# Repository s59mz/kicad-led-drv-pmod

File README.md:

# led_drv_pmod
PMOD PCB module for LTC3206 LED driver 

Schematic:
[led_drv_pmod.pdf](led_drv_pmod.pdf)

BOM:
[led_drv_pmod.csv](led_drv_pmod.csv)

Gerbers:
[gerbers.zip](https://github.com/s59mz/kicad-led-drv-pmod/raw/main/gerbers.zip)

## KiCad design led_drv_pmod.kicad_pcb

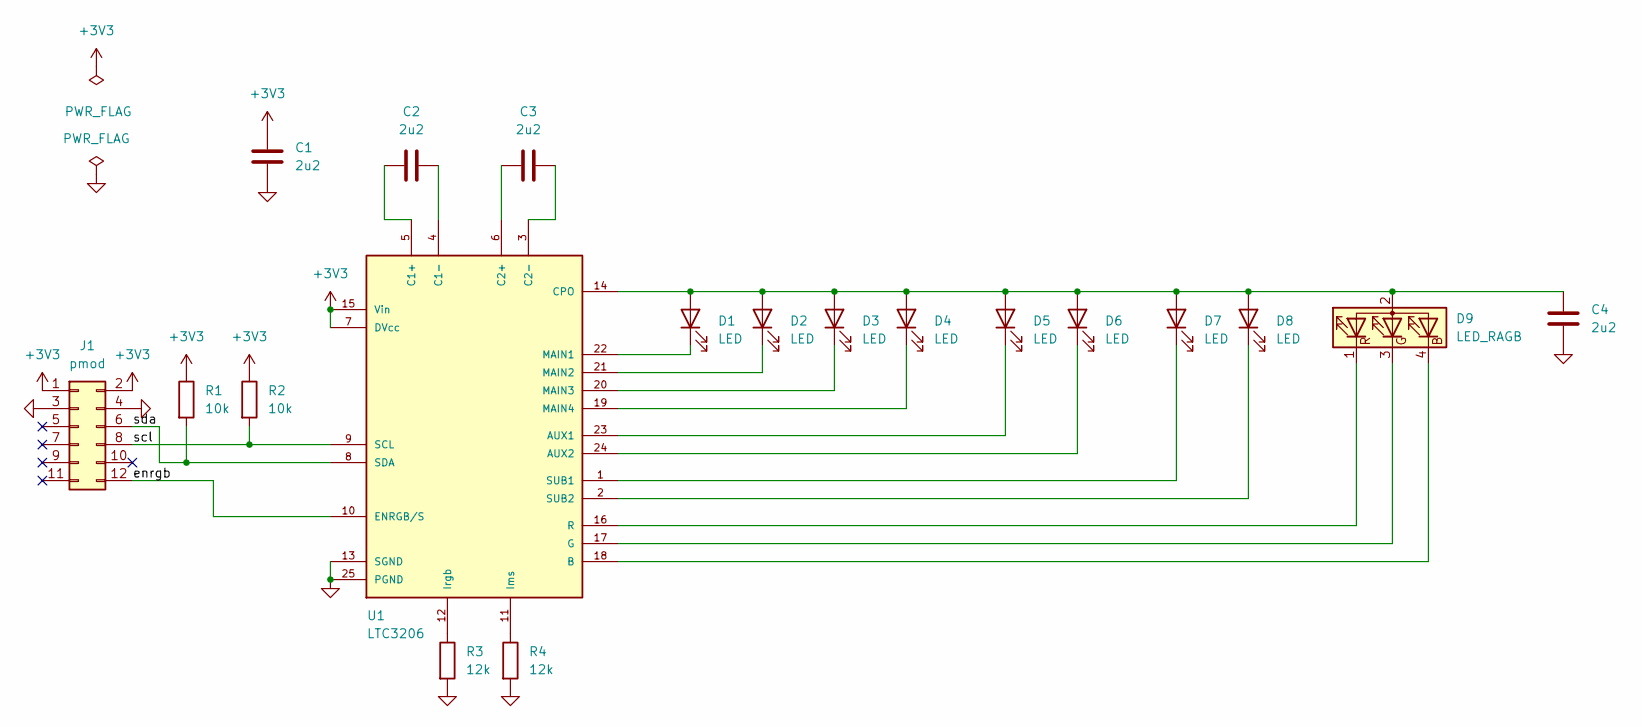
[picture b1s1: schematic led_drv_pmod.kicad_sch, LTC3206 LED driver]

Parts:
C1, C2, C3, C4: 2u2; C_0603_1608Metric_Pad1.08x0.95mm_HandSolder
D1, D2, D3, D4: LED; LED_D3.0mm_Clear
D5, D6, D7, D8: LED; LED_D3.0mm
D9: LED_RAGB; LED_D5.0mm-4_RGB
J1: pmod; PinHeader_2x06_P2.54mm_Horizontal
R1, R2: 10k; R_0603_1608Metric_Pad0.98x0.95mm_HandSolder
R3, R4: 12k; R_0603_1608Metric_Pad0.98x0.95mm_HandSolder
U1: LTC3206; QFN-24; PARTREV 02/18/2014

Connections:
+3V3: C1.1, J1.1, J1.2, R1.1, R2.1, U1.7 (DVcc), U1.15 (Vin)
/enrgb: J1.12, U1.10 (ENRGB/S)
/scl: J1.8, R2.2, U1.9 (SCL)
/sda: J1.6, R1.2, U1.8 (SDA)
GND: C1.2, C4.2, J1.3, J1.4, R3.2, R4.2, U1.13 (SGND), U1.25 (PGND)
unnamed: C2.1, U1.4 (C1-)
unnamed: C2.2, U1.5 (C1+)
unnamed: C3.1, U1.3 (C2-)
unnamed: C3.2, U1.6 (C2+)
unnamed: C4.1, D1.2 (A), D2.2 (A), D3.2 (A), D4.2 (A), D5.2 (A), D6.2 (A), D7.2 (A), D8.2 (A), D9.2 (A), U1.14 (CPO)
unnamed: D1.1 (K), U1.22 (MAIN1)
unnamed: D2.1 (K), U1.21 (MAIN2)
unnamed: D3.1 (K), U1.20 (MAIN3)
unnamed: D4.1 (K), U1.19 (MAIN4)
unnamed: D5.1 (K), U1.23 (AUX1)
unnamed: D6.1 (K), U1.24 (AUX2)
unnamed: D7.1 (K), U1.1 (SUB1)
unnamed: D8.1 (K), U1.2 (SUB2)
unnamed: D9.1 (RK), U1.16 (R)
unnamed: D9.3 (GK), U1.17 (G)
unnamed: D9.4 (BK), U1.18 (B)
unnamed: R3.1, U1.12 (Irgb)
unnamed: R4.1, U1.11 (Ims)

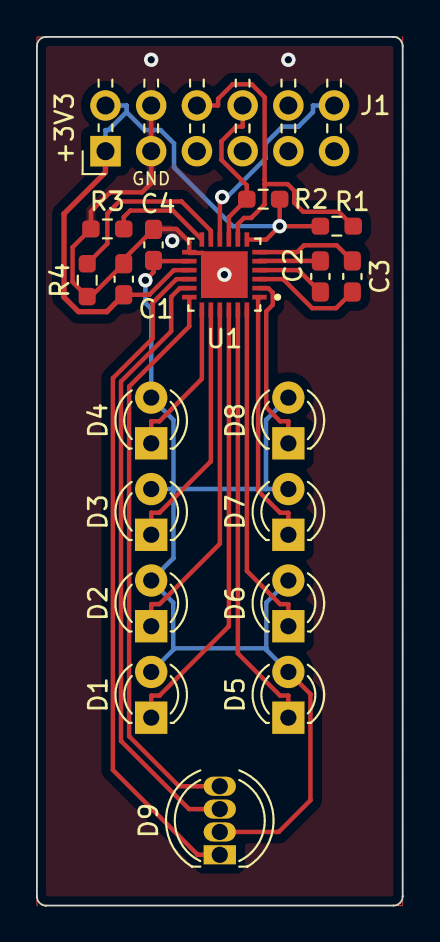
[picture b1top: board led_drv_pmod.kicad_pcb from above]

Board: 2 copper layers, 20.3 x 48.3 mm, 19 parts (0 on the bottom side), 23 nets.

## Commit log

2023-03-08 fixed block capacitor and i2c pull up
2024-08-11 add screenshots
